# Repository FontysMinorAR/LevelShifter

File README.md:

This is an application for the Arduino Nano to test the Level shifter Board

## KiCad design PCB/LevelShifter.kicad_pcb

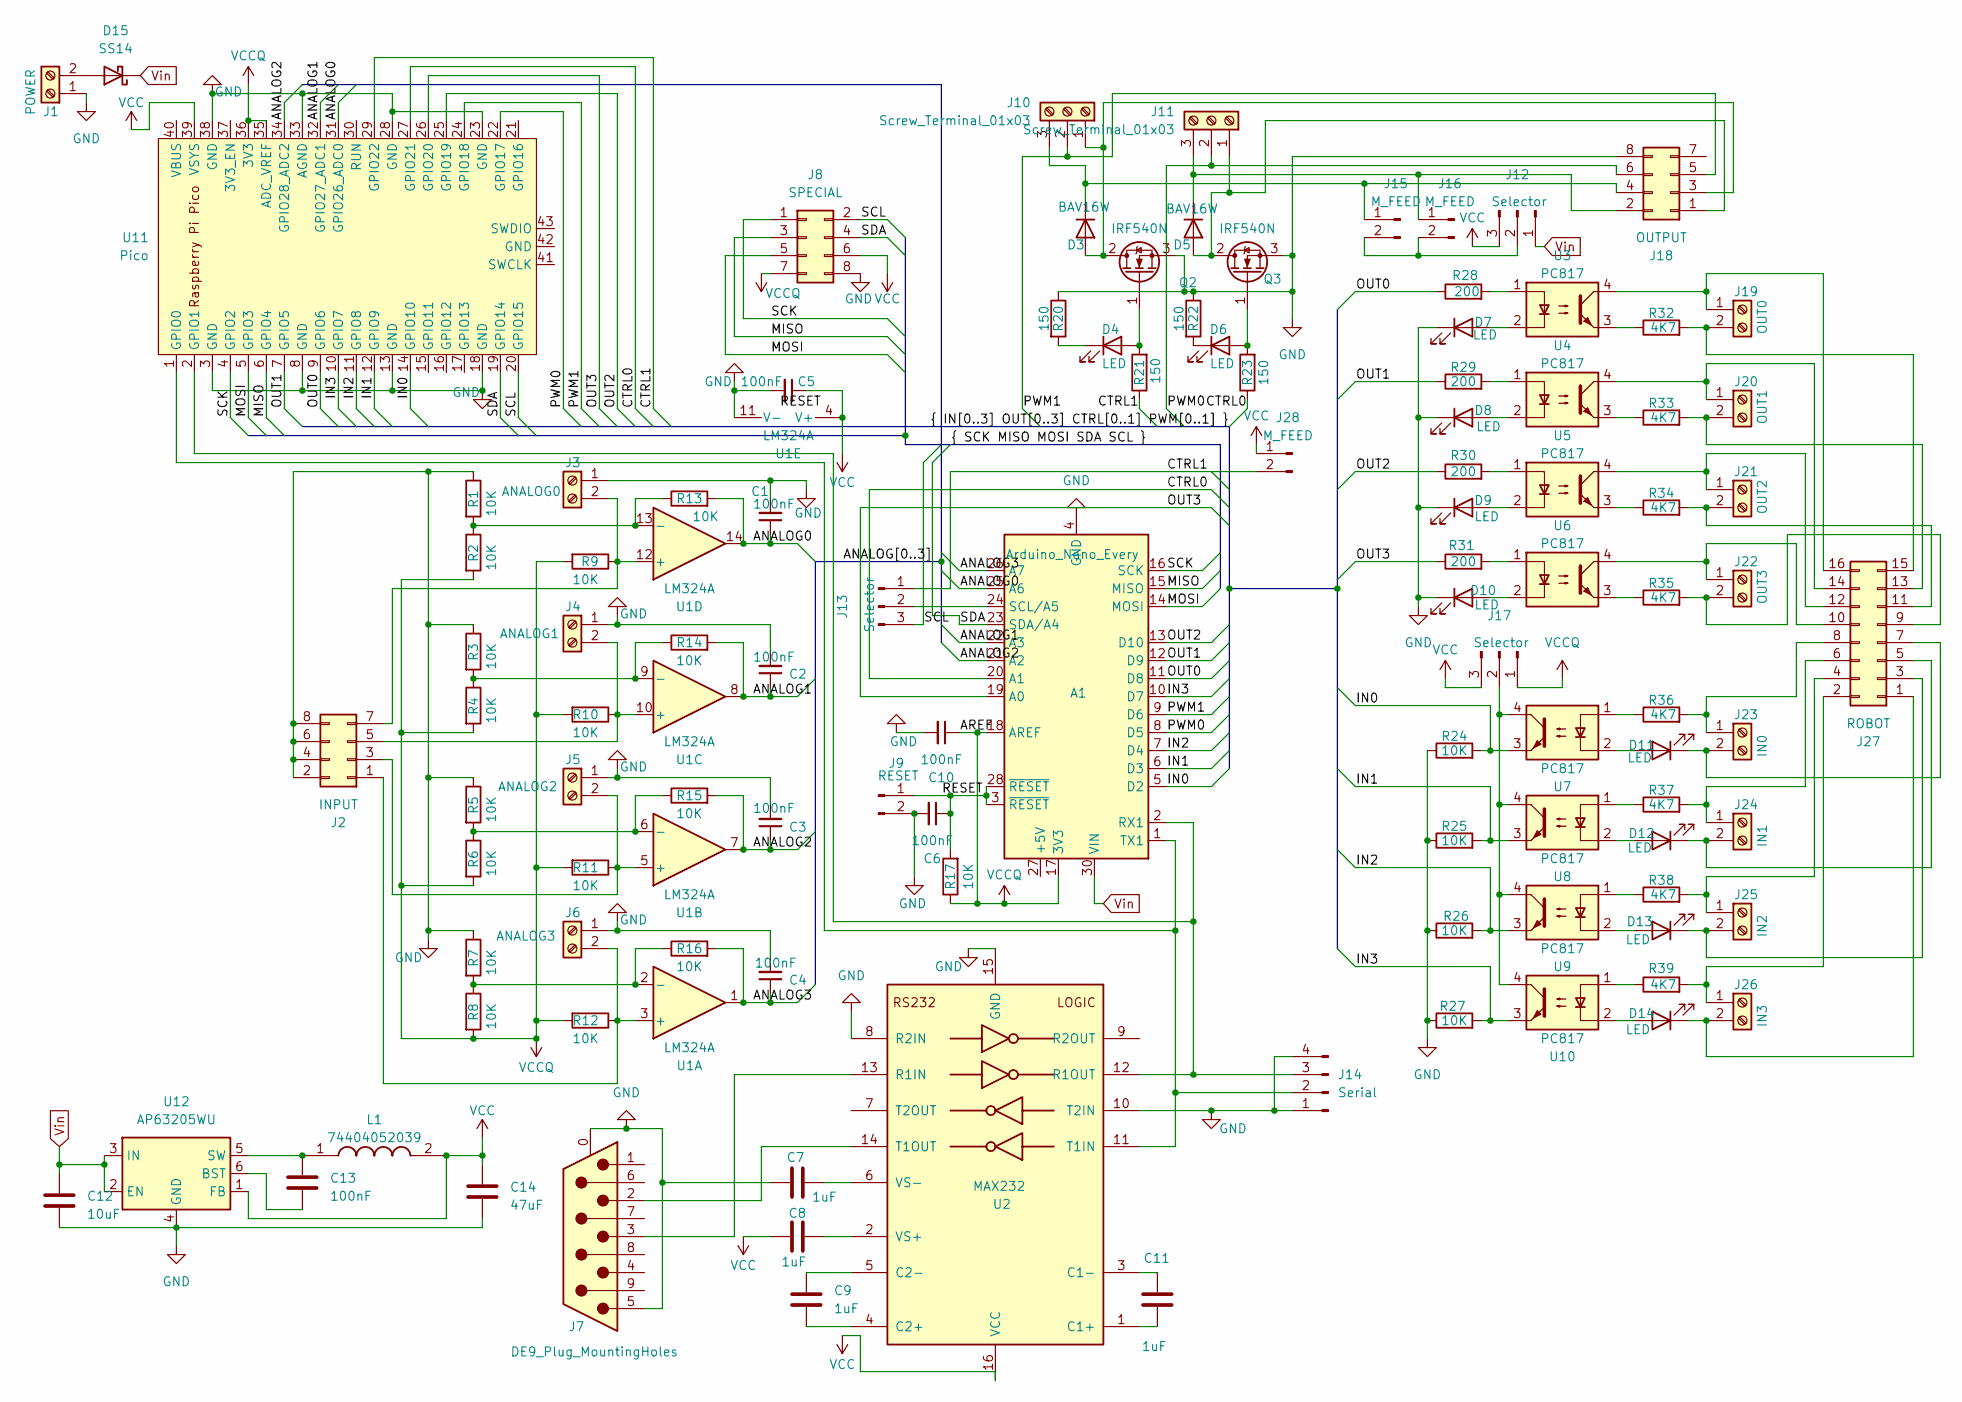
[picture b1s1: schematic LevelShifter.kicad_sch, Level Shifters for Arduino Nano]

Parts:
A1: Arduino_Nano_Every; Arduino_Nano
C1, C2, C3, C4, C5, C6, C10: 100nF; C_0805_2012Metric
C7, C8, C9, C11: 1uF; C_1206_3216Metric_Pad1.33x1.80mm_HandSolder
C12: 10uF; C_1206_3216Metric_Pad1.33x1.80mm_HandSolder
C13: 100nF; C_0805_2012Metric_Pad1.18x1.45mm_HandSolder
C14: 47uF; C_1206_3216Metric_Pad1.33x1.80mm_HandSolder
D3, D5: BAV16W; D_SOD-123
D4, D6, D7, D8, D9, D10, D11, D12, D13, D14: LED; LED_D5.0mm
D15: SS14; D_SMA
J1: POWER; TerminalBlock_MetzConnect_Type101_RT01602HBWC_1x02_P5.08mm_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
J2: INPUT; PinSocket_2x04_P2.54mm_Vertical
J3: ANALOG0; TerminalBlock_MetzConnect_Type101_RT01602HBWC_1x02_P5.08mm_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
J4: ANALOG1; TerminalBlock_MetzConnect_Type101_RT01602HBWC_1x02_P5.08mm_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
J5: ANALOG2; TerminalBlock_MetzConnect_Type101_RT01602HBWC_1x02_P5.08mm_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
J6: ANALOG3; TerminalBlock_MetzConnect_Type101_RT01602HBWC_1x02_P5.08mm_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
J7: DE9_Plug_MountingHoles; DSUB-9_Female_Horizontal_P2.77x2.84mm_EdgePinOffset4.94mm_H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
J8: SPECIAL; PinSocket_2x04_P2.54mm_Vertical
J9: RESET; PinSocket_1x02_P2.54mm_Vertical
J10, J11: Screw_Terminal_01x03; TerminalBlock_MetzConnect_Type011_RT05503HBWC_1x03_P5.00mm_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
J12, J13, J17: Selector; PinHeader_1x03_P2.54mm_Vertical
J14: Serial; PinSocket_1x04_P2.54mm_Vertical
J15, J16, J28: M_FEED; PinSocket_1x02_P2.54mm_Vertical
J18: OUTPUT; PinSocket_2x04_P2.54mm_Vertical
J19: OUT0; TerminalBlock_MetzConnect_Type101_RT01602HBWC_1x02_P5.08mm_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
J20: OUT1; TerminalBlock_MetzConnect_Type101_RT01602HBWC_1x02_P5.08mm_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
J21: OUT2; TerminalBlock_MetzConnect_Type101_RT01602HBWC_1x02_P5.08mm_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
J22: OUT3; TerminalBlock_MetzConnect_Type101_RT01602HBWC_1x02_P5.08mm_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
J23: IN0; TerminalBlock_MetzConnect_Type101_RT01602HBWC_1x02_P5.08mm_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
J24: IN1; TerminalBlock_MetzConnect_Type101_RT01602HBWC_1x02_P5.08mm_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
J25: IN2; TerminalBlock_MetzConnect_Type101_RT01602HBWC_1x02_P5.08mm_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
J26: IN3; TerminalBlock_MetzConnect_Type101_RT01602HBWC_1x02_P5.08mm_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
J27: ROBOT; PinSocket_2x08_P2.54mm_Vertical
L1: 74404052039; CD75; Manufacturer_Part_Number 74404052039
Q2, Q3: IRF540N; TO-220-3_Vertical
R1, R2, R3, R4, R5, R6, R7, R8, R9, R10, R11, R12, R13, R14, R15, R16, R17, R24, R25, R26, R27: 10K; R_Axial_DIN0207_L6.3mm_D2.5mm_P7.62mm_Horizontal
R20, R21, R22, R23: 150; R_Axial_DIN0207_L6.3mm_D2.5mm_P7.62mm_Horizontal
R28, R29, R30, R31: 200; R_Axial_DIN0207_L6.3mm_D2.5mm_P7.62mm_Horizontal
R32, R33, R34, R35, R36, R37, R38, R39: 4K7; R_Axial_DIN0207_L6.3mm_D2.5mm_P7.62mm_Horizontal
U1: LM324A; DIP-14_W7.62mm
U2: MAX232; DIP-16_W7.62mm
U3, U4, U5, U6, U7, U8, U9, U10: PC817; DIP-4_W7.62mm
U11: Pico; pico
U12: AP63205WU; TSOT-23-6

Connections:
/ANALOG0: A1.25 (A6), C1.1, R13.2, U1.14, U11.31 (GPIO26_ADC0)
/ANALOG1: A1.22 (A3), C2.1, R14.2, U1.8, U11.32 (GPIO27_ADC1)
/ANALOG2: A1.21 (A2), C3.1, R15.2, U1.7, U11.34 (GPIO28_ADC2)
/ANALOG3: A1.26 (A7), C4.1, R16.2, U1.1
/CTRL0: A1.20 (A1), R23.1, U11.27 (GPIO21)
/CTRL1: J13.1, J28.2, R21.1, U11.29 (GPIO22)
/IN0: A1.5 (D2), R24.2, U7.3, U11.14 (GPIO10)
/IN1: A1.6 (D3), R25.2, U8.3, U11.12 (GPIO9)
/IN2: A1.7 (D4), R26.2, U9.3, U11.11 (GPIO8)
/IN3: A1.10 (D7), R27.2, U10.3, U11.10 (GPIO7)
/MISO: A1.15 (MISO), J8.3, U11.6 (GPIO4)
/MOSI: A1.14 (MOSI), J8.5, U11.5 (GPIO3)
/OUT0: A1.11 (D8), R28.1, U11.9 (GPIO6)
/OUT1: A1.12 (D9), R29.1, U11.7 (GPIO5)
/OUT2: A1.13 (D10), R30.1, U11.25 (GPIO19)
/OUT3: A1.19 (A0), R31.1, U11.26 (GPIO20)
/PWM0: A1.8 (D5), J11.2, J18.6, U11.22 (GPIO17)
/PWM1: A1.9 (D6), J10.2, J18.5, U11.24 (GPIO18)
/RESET: A1.3 (~RESET), A1.28 (~RESET), C6.1, J9.1, R17.2
/SCK: A1.16 (SCK), J8.1, U11.4 (GPIO2)
/SCL: J8.2, J13.3, U11.20 (GPIO15)
/SDA: A1.23 (SDA/A4), J8.4, U11.19 (GPIO14)
GND: A1.4 (GND), A1.29 (GND), C1.2, C2.2, C3.2, C4.2, C5.2, C6.2, C7.1, C10.2, C12.2, C14.2, D7.1 (K), D8.1 (K), D9.1 (K), D10.1 (K), J1.1, J2.2, J2.4, J2.6, J2.8, J3.1, J4.1, J5.1, J6.1, J7.0 (PAD), J7.5, J8.8, J9.2, J14.1, J14.4, J18.8, Q2.3 (S), Q3.3 (S), R1.1, R3.1, R5.1, R7.1, R20.1, R22.1, R24.1, R25.1, R26.1, R27.1, U1.11 (V-), U2.8 (R2IN), U2.10 (T2IN), U2.15 (GND), U11.3 (GND), U11.8 (GND), U11.13 (GND), U11.18 (GND), U11.23 (GND), U11.28 (GND), U11.33 (AGND), U11.38 (GND), U12.4 (GND)
unnamed: A1.2 (RX1), J14.3, U2.12 (R1OUT), U11.2 (GPIO1)
unnamed: A1.24 (SCL/A5), J13.2
unnamed: A1.1 (TX1), J14.2, U2.11 (T1IN), U11.1 (GPIO0)
unnamed: D3.2 (A), J10.1, J18.3, Q2.2 (D)
unnamed: D3.1 (K), J10.3, J15.1, J18.4
unnamed: D4.2 (A), Q2.1 (G), R21.2
unnamed: D4.1 (K), R20.2
unnamed: D5.2 (A), J11.1, J18.1, Q3.2 (D)
unnamed: D5.1 (K), J11.3, J16.1, J18.2
unnamed: D6.2 (A), Q3.1 (G), R23.2
unnamed: D6.1 (K), R22.2
unnamed: D7.2 (A), U3.2
unnamed: D8.2 (A), U4.2
unnamed: D9.2 (A), U5.2
unnamed: D10.2 (A), U6.2
unnamed: D11.2 (A), U7.2
unnamed: D11.1 (K), J23.2, J27.7
unnamed: D12.2 (A), U8.2
unnamed: D12.1 (K), J24.2, J27.5
unnamed: D13.2 (A), U9.2
unnamed: D13.1 (K), J25.2, J27.3
unnamed: D14.2 (A), U10.2
unnamed: D14.1 (K), J26.2, J27.1
unnamed: D15.2 (A), J1.2
unnamed: J2.1, J6.2, R12.1, U1.3 (+)
unnamed: J2.3, J5.2, R11.1, U1.5 (+)
unnamed: J2.5, J4.2, R10.1, U1.10 (+)
unnamed: J2.7, J3.2, R9.1, U1.12 (+)
unnamed: J12.2, J15.2, J16.2
unnamed: J17.2, U7.4, U8.4, U9.4, U10.4
unnamed: J19.1, J27.16, U3.4
unnamed: J19.2, J27.15, R32.2
unnamed: J20.1, J27.14, U4.4
unnamed: J20.2, J27.13, R33.2
unnamed: J21.1, J27.12, U5.4
unnamed: J21.2, J27.11, R34.2
unnamed: J22.1, J27.10, U6.4
unnamed: J22.2, J27.9, R35.2
unnamed: J23.1, J27.8, R36.2
unnamed: J24.1, J27.6, R37.2
unnamed: J25.1, J27.4, R38.2
unnamed: J26.1, J27.2, R39.2
unnamed: R28.2, U3.1
unnamed: R29.2, U4.1
unnamed: R30.2, U5.1
unnamed: R31.2, U6.1
unnamed: R32.1, U3.3
unnamed: R33.1, U4.3
unnamed: R34.1, U5.3
unnamed: R35.1, U6.3
unnamed: R36.1, U7.1
unnamed: R37.1, U8.1
unnamed: R38.1, U9.1
unnamed: R39.1, U10.1
unnamed: R7.2, R8.1, R16.1, U1.2 (-)
unnamed: R5.2, R6.1, R15.1, U1.6 (-)
unnamed: R3.2, R4.1, R14.1, U1.9 (-)
unnamed: R1.2, R2.1, R13.1, U1.13 (-)
unnamed: C11.1, U2.1 (C1+)
unnamed: C11.2, U2.3 (C1-)
unnamed: C9.1, U2.4 (C2+)
unnamed: C9.2, U2.5 (C2-)
unnamed: J7.3, U2.13 (R1IN)
unnamed: J7.2, U2.14 (T1OUT)
unnamed: C8.2, U2.2 (VS+)
unnamed: C7.2, U2.6 (VS-)
unnamed: C13.2, U12.6 (BST)
unnamed: C13.1, L1.1, U12.5 (SW)
VCC: C5.1, C8.1, C14.1, J8.6, J12.3, J17.3, J28.1, L1.2, U1.4 (V+), U2.16 (VCC), U11.39 (VSYS), U12.1 (FB)
VCCQ: A1.17 (3V3), A1.18 (AREF), C10.1, J8.7, J17.1, R2.2, R4.2, R6.2, R8.2, R9.2, R10.2, R11.2, R12.2, R17.1, U11.35 (ADC_VREF), U11.36 (3V3)
Vin: A1.30 (VIN), C12.1, D15.1 (K), J12.1, U12.2 (EN), U12.3 (IN)

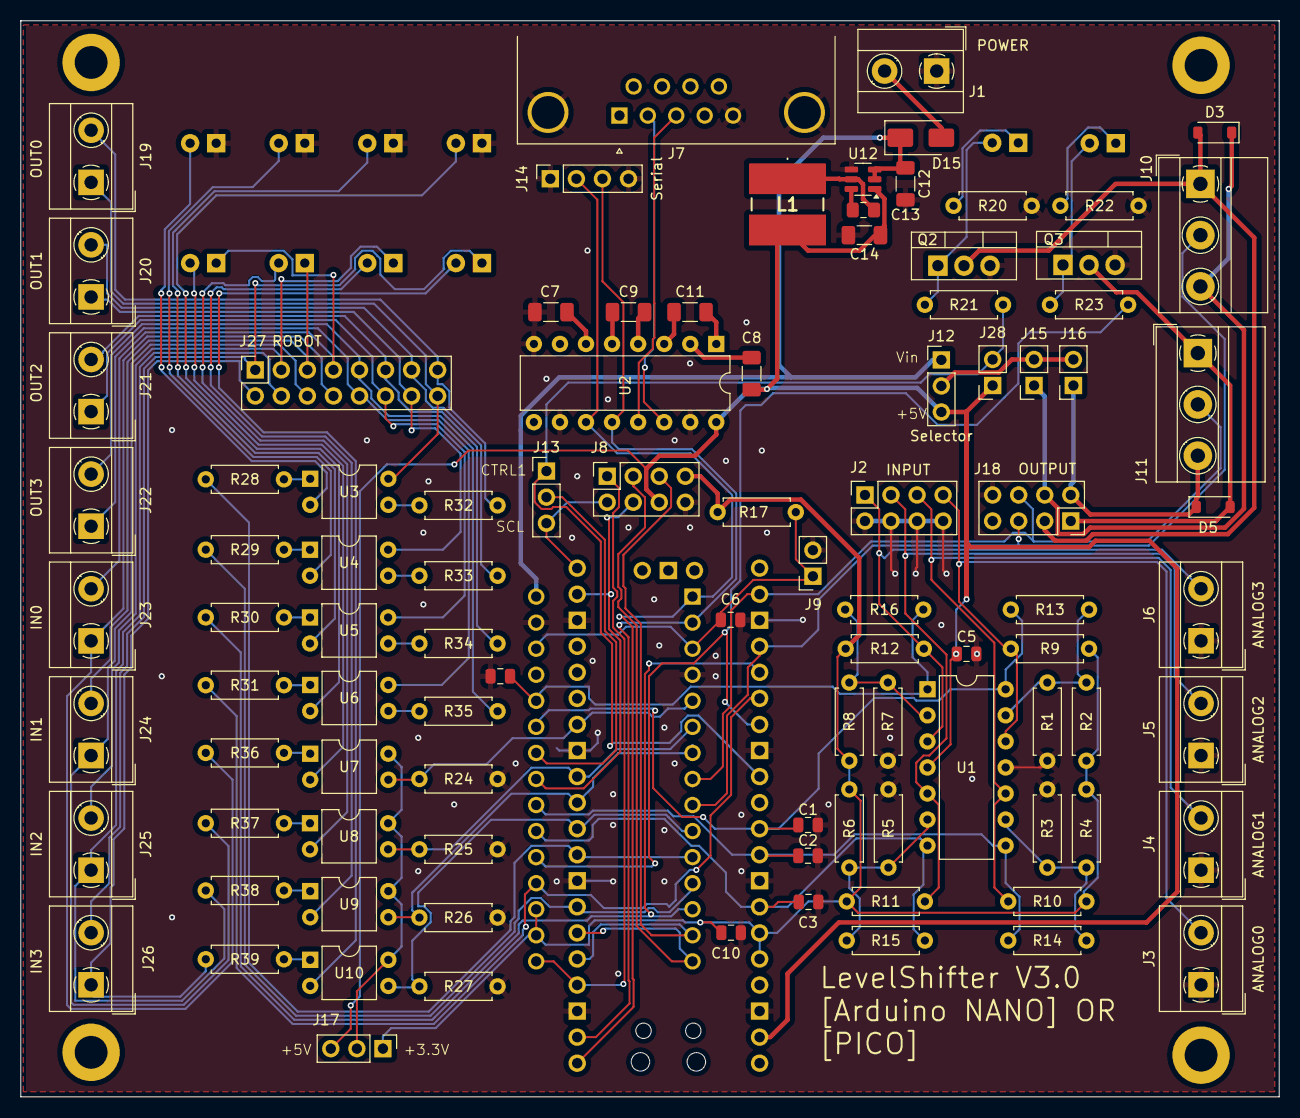
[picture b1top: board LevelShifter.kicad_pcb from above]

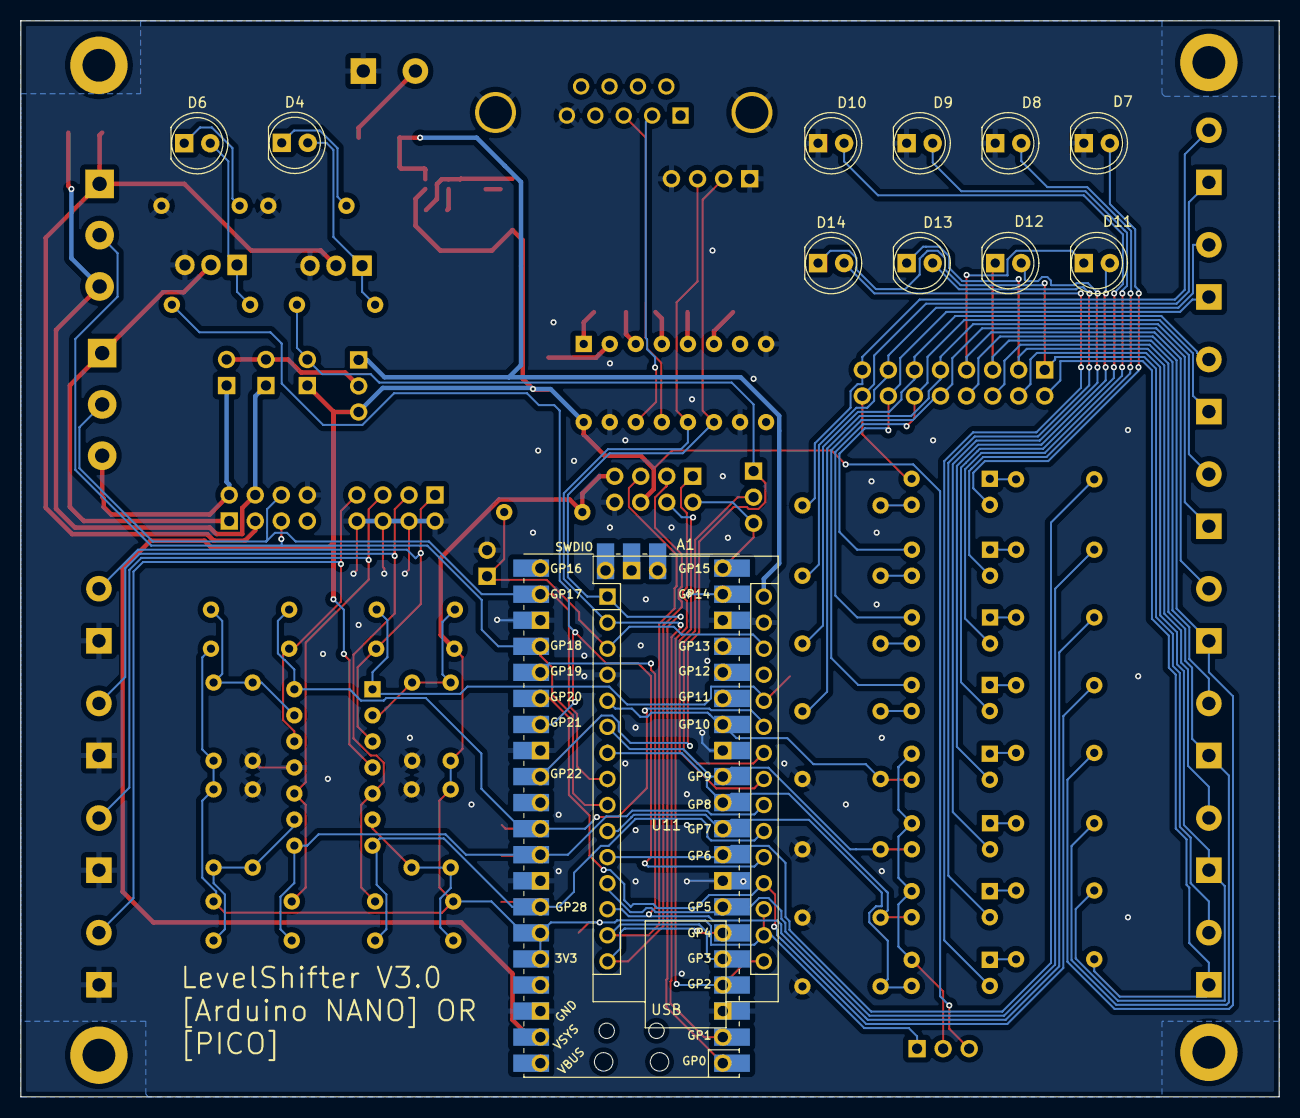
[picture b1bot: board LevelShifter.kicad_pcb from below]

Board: 2 copper layers, 122.7 x 104.9 mm, 108 parts (12 on the bottom side), 94 nets.

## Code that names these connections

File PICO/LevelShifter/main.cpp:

#include <stdio.h>
#include <ctype.h>
#include <stdlib.h>
#include <cstring>
#include <pico/stdlib.h>
#include <pico/stdio_usb.h>
#include <hardware/adc.h>

#include "pwmpin.h"

static void state_change (const uint8_t pinId, const uint32_t events);

static const int MinimumFrequency = 20000;

static NextGen::IOPin   out0(6);
static NextGen::IOPin   out1(5);
static NextGen::IOPin   out2(19);
static NextGen::IOPin   out3(20);
static NextGen::IOPin   in0(10, state_change, NextGen::trigger_mode::BOTH, true);
static NextGen::IOPin   in1(9, state_change, NextGen::trigger_mode::BOTH, true);
static NextGen::IOPin   in2(8, state_change, NextGen::trigger_mode::BOTH, true);
static NextGen::IOPin   in3(7, state_change, NextGen::trigger_mode::BOTH, true);
static NextGen::PWMPin  PWMPin0(17);
static NextGen::PWMPin  PWMPin1(18);
static NextGen::IOPin   ctrl0(21);
static NextGen::IOPin   ctrl1(22);

// Analog0 => 26
// Analog1 => 27
// Analog1 => 28


static void show_pin_details(const uint8_t pin) {
    const char* pullUp = (gpio_is_pulled_up(pin) ? " up " : gpio_is_pulled_down(pin) ? "down" : "    ");
    const char* direction = (gpio_get_dir(pin) == 1 ? "out" : "in ");
    const char* value = gpio_get(pin) ? "true " : "false";
    const char* mode = "????";
    const char* strength = "?? mA";
    const char* slew = "????";

    switch(gpio_get_slew_rate(pin)) {
        case GPIO_SLEW_RATE_SLOW: slew = "slow"; break;
        case GPIO_SLEW_RATE_FAST: slew = "fast"; break;
    }

    switch (gpio_get_drive_strength(pin)) {
        case GPIO_DRIVE_STRENGTH_2MA:  strength = " 2 mA"; break;
        case GPIO_DRIVE_STRENGTH_4MA:  strength = " 4 mA"; break;
        case GPIO_DRIVE_STRENGTH_8MA:  strength = " 8 mA"; break;
        case GPIO_DRIVE_STRENGTH_12MA: strength = "12 mA"; break;
    }

    switch(gpio_get_function(pin)){
        case GPIO_FUNC_XIP:  mode = "XIP "; break;
        case GPIO_FUNC_SPI:  mode = "SPI "; break;
        case GPIO_FUNC_UART: mode = "UART"; break;
        case GPIO_FUNC_I2C:  mode = "I2C "; break;
        case GPIO_FUNC_PWM:  mode = "PWM "; break; 
        case GPIO_FUNC_SIO:  mode = "SIO "; break;
        case GPIO_FUNC_PIO0: mode = "PIO0"; break;
        case GPIO_FUNC_PIO1: mode = "PIO1"; break;
        case GPIO_FUNC_GPCK: mode = "GPCK"; break; 
        case GPIO_FUNC_USB:  mode = "USB "; break;
        case GPIO_FUNC_NULL: mode = "NULL"; break;
    }

    printf("Pin: [%02d], Value: [%s], Mode: [%s], Pull: [%s], Dir: [%s], Strength: [%s], Slew: [%s]\n", pin, value, mode, pullUp, direction, strength, slew);
}

static void pin_overview () {
    for (uint8_t index = 0; index <= 22; index++) {
        show_pin_details(index);
    }
    for (uint8_t index = 25; index <= 28; index++) {
        show_pin_details(index);
    }
}

static void state_change (const uint8_t pinId, const uint32_t events) {
    printf ("Triggered pin [%d]\n", pinId);
}

static uint8_t check_mode(const char buffer[]) {
    uint8_t result = ~0;
    if (::toupper(buffer[0]) == 'O') {
        char next = ::toupper(buffer[1]);
        if (next == 'N') {
            result = 1;
        }
        else if ((next == 'F') && (::toupper(buffer[2]) == 'F')) {
            result = 0;
        }
    }
    return (result);
}

static uint8_t RunSlots = 5;
static uint8_t TimeSlot = 100;

static void LoopADC(const uint8_t id) {
    uint32_t key;
    uint8_t slots = 0;
  
    printf("\nPolling ADC%c every %d millisecond\n", (id == 16 ? 'X' : '0' + id), TimeSlot * RunSlots);
    adc_gpio_init(26 + id);
    adc_select_input(id);
    do {
        key = getchar_timeout_us(TimeSlot * 1000);
        if ( (key == PICO_ERROR_TIMEOUT) && (slots == RunSlots) )  {
            slots = 0;
            uint16_t value = adc_read();
            printf("Value: %d\n", value);
        }
        else {
            slots++;
        }
    } while (key == PICO_ERROR_TIMEOUT);
    printf ("Stopped reading ADC%d\n", id);
}

int main(){
    stdio_usb_init(); // init usb only. uart0 and uart1 are needed elsewhere

    while(!stdio_usb_connected()); // wait until USB connection

    printf("Firing up the Enhanced C world Controller!!\n>>");

    uint8_t index = 0;
    char buffer[64];

    PWMPin0.Enabled(false);
    PWMPin0.Frequency(25000);
    adc_init();

    // main loop
    while(1){
        int result = getchar_timeout_us(10);

        if (result != PICO_ERROR_TIMEOUT) {
            if (::isprint(result)) {
                if (index < sizeof(buffer)) {
                    printf("%c", result);
                    buffer[index++] = (char) result;
                }
            }
            else if(index == 0) {
                printf("\nThere is no data to process\n>>");
            }
            else if (result == 8) {
                printf("%c", result);
                index--;
            }
            else if (strncmp(buffer, "ADC0",4) == 0) {
                index = 0;
                LoopADC(0);
            }
            else if (strncmp(buffer, "ADC1", 4) == 0) {
                index = 0;
                LoopADC(1);
            }
            else if (strncmp(buffer, "ADC2", 4) == 0) {
                index = 0;
                LoopADC(2);
            }
            else if (strncmp(buffer, "Pins", 4) == 0) {
                index = 0;
                printf("\n");
                pin_overview();
            }
            else if (buffer[0] == '0') {
                uint8_t mode = check_mode(&buffer[1]);
                if (mode != 0xFF) {
                    printf("\nSet OUT0: %s", mode == 1 ? "On" : "Off");
                    out0.Set(mode == 1);
                }
                printf("\n");
                index = 0;
            }
            else if (buffer[0] == '1') {
                uint8_t mode = check_mode(&buffer[1]);
                if (mode != 0xFF) {
                    printf("\nSet OUT1: %s", mode == 1 ? "On" : "Off");
                    out1.Set(mode == 1);
                }
                printf("\n");
                index = 0;
            }
            else if (buffer[0] == '2') {
                uint8_t mode = check_mode(&buffer[1]);
                if (mode != 0xFF) {
                    printf("\nSet OUT2: %s", mode == 1 ? "On" : "Off");
                    out2.Set(mode == 1);
                }
                printf("\n");
                index = 0;
            }
            else if (buffer[0] == '3') {
                uint8_t mode = check_mode(&buffer[1]);
                if (mode != 0xFF) {
                    printf("\nSet OUT3: %s", mode == 1 ? "On" : "Off");
                    out3.Set(mode == 1);
                }
                printf("\n");
                index = 0;
            }
            else if (buffer[0] == 'i') {
                printf("\nIN0 = %s", in0.Get() ? "On" : "Off");
                printf("\nIN1 = %s", in1.Get() ? "On" : "Off");
                printf("\nIN2 = %s", in2.Get() ? "On" : "Off");
                printf("\nIN3 = %s", in3.Get() ? "On" : "Off");
                printf("\n");
                index = 0;
            }
            else if (buffer[0] == '?') {
                printf("\nOptions for the Sofware:");
                printf("\n{0<on|off>} Set OUT0 on or off");
                printf("\n{2<on|off>} Set OUT1 on or off");
                printf("\n{3<on|off>} Set OUT2 on or off");
                printf("\n{4<on|off>} Set OUT3 on or off");
                printf("\n{4<on|off>} Set OUT3 on or off");
                printf("\n{i} Show status of IN0,IN1,IN2,IN3");
                printf("\n[?] Show this help\n>>");
                index = 0;
            }
            else {
                buffer[index] = '\0';
                printf("\nUncomprehandable data: [%s]\n>>", buffer);
                index = 0;
            }
        }
    }
    return 0;
}

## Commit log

2024-08-13 [INITIAL] Initial commit
2024-08-13 [CLEANUP] Removed duplicate code
2024-08-13 [Functionalities] servomotor & forceSensor
2024-08-20 [SYNC] Initial commit of the level shifter. Still need to fill in the sleected resitor values.
2024-09-01 [ARDUINO] Make PWM available for Servo motor (5V from buck circuit. PW on pinout) [PICO] Allow design for RaspberryPi Pico placement
2024-09-02 [UPDATE] outing done. Start the final touch!
2024-09-02 [COMPLETED] All tracks laid. Wiaitng for the production of the PCB.
2024-12-04 [TESTED]
2024-12-04 Schema a PDF
2024-12-04 [NEW] PCB layout as PDF
2025-02-07 [PICO[ Add a PIC C code example for the LevelShifter PCB.
2025-06-01 [SYNC]
